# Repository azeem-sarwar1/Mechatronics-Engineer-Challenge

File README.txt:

KiCad PCB Design – Evaluation Task

This repository contains the PCB design created as part of the evaluation task using **KiCad**.

## 📌 Task Overview
1. **PCB Creation**
   - Added components:
     - Default KiCad LED symbol with footprint and 3D model is downloaded and modified.
     - Custom symbol + footprint for **TCAN4551-Q1** (VQFN-20 package) and 3D model is download.
     - Default KiCad symbol **MCIMX6D4AVT**.
     - Verified footprints with 3D viewer and picture attached.

2. **Custom Libraries**
   - Created a **custom symbol library** (`tcan4551-q1.kicad_sym`).
   - Created a **custom footprint library** (`TCAN4551_VQFN20.kicad_mod`).
   - Linked symbol and footprint.
   - 3D model is download.

3. **Design Rules**
   - Applied custom microvia design rules:
     - Minimum annular width: **2 mil**
     - Minimum via diameter: **8 mil**
     - Minimum via hole: **4 mil**

4. **Bonus**
   - Library for **TCAN4551-Q1** also stored in a separate repository, which can be mounted as a submodule.
    This project uses the TCAN4551 library. Download it separately from, https://github.com/azeem-sarwar1/TCAN4551-Q1_Library.git

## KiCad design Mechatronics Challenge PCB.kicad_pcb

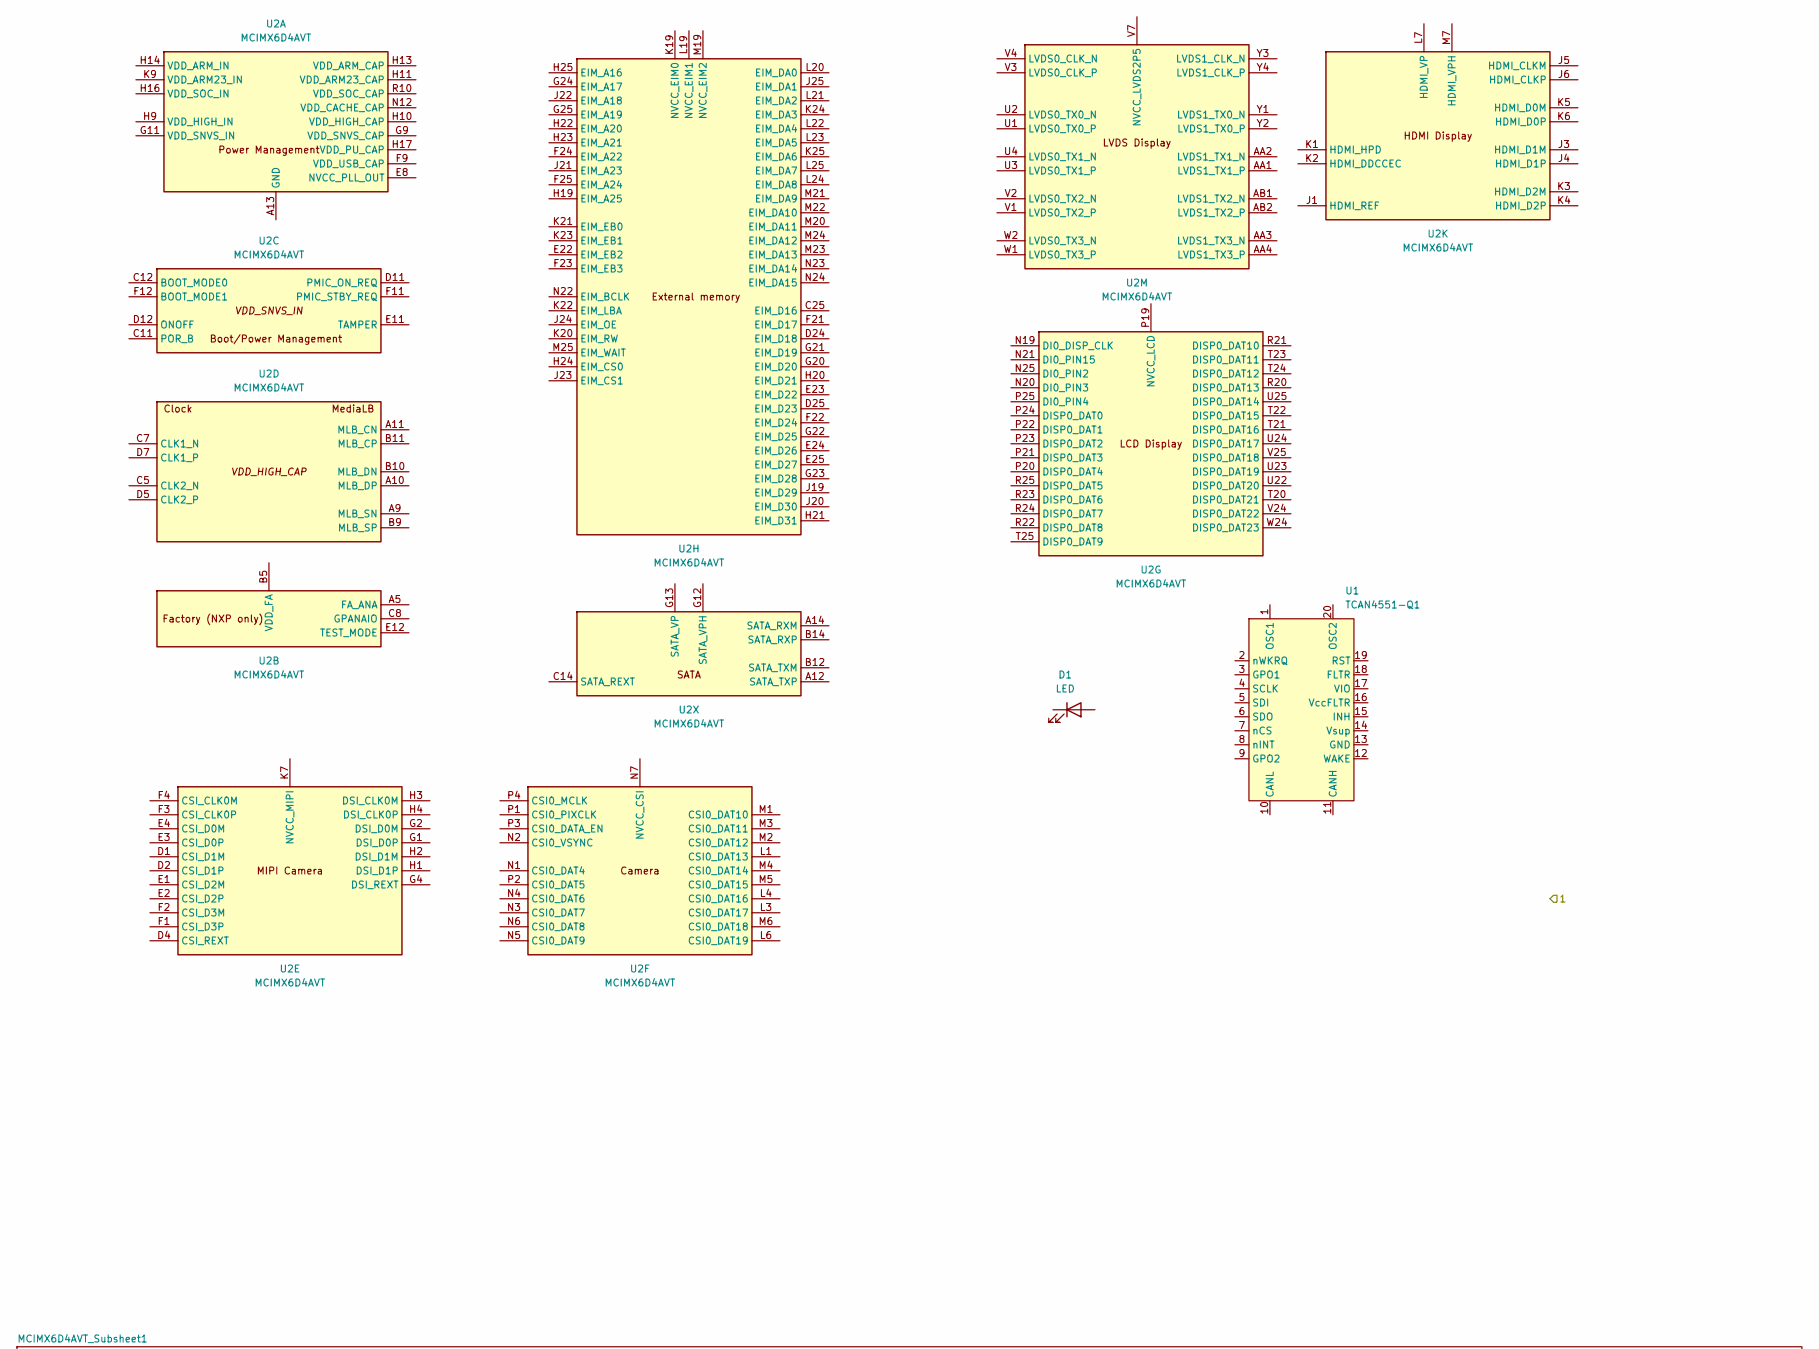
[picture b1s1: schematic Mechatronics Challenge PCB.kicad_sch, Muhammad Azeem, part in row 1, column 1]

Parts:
D1: LED; LED_miniPLCC_2315
U1: TCAN4551-Q1; TCAN4551_VQFN20
U2: MCIMX6D4AVT; BGA-624_21x21mm_Layout25x25_P0.8mm

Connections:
unnamed: U2.A4 (GND), U2.A8 (GND), U2.A13 (GND), U2.A25 (GND), U2.AA7 (GND), U2.AA10 (GND), U2.AA13 (GND), U2.AA16 (GND), U2.AA19 (GND), U2.AA22 (GND), U2.AB3 (GND), U2.AB24 (GND), U2.AD4 (GND), U2.AD7 (GND), U2.AD10 (GND), U2.AD13 (GND), U2.AD16 (GND), U2.AD19 (GND), U2.AD22 (GND), U2.AE1 (GND), U2.AE25 (GND), U2.B4 (GND), U2.C1 (GND), U2.C4 (GND), U2.C6 (GND), U2.C10 (GND), U2.D3 (GND), U2.D6 (GND), U2.D8 (GND), U2.E5 (GND), U2.E6 (GND), U2.E7 (GND), U2.F5 (GND), U2.F6 (GND), U2.F7 (GND), U2.F8 (GND), U2.G3 (GND), U2.G10 (GND), U2.G19 (GND), U2.H8 (GND), U2.H12 (GND), U2.H15 (GND), U2.H18 (GND), U2.J2 (GND), U2.J8 (GND), U2.J12 (GND), U2.J15 (GND), U2.J18 (GND), U2.K8 (GND), U2.K10 (GND), U2.K12 (GND), U2.K15 (GND), U2.K18 (GND), U2.L2 (GND), U2.L5 (GND), U2.L8 (GND), U2.L10 (GND), U2.L12 (GND), U2.L15 (GND), U2.L18 (GND), U2.M8 (GND), U2.M10 (GND), U2.M12 (GND), U2.M15 (GND), U2.M18 (GND), U2.N8 (GND), U2.N10 (GND), U2.N15 (GND), U2.N18 (GND), U2.P8 (GND), U2.P10 (GND), U2.P12 (GND), U2.P15 (GND), U2.P18 (GND), U2.R8 (GND), U2.R12 (GND), U2.R15 (GND), U2.R17 (GND), U2.T8 (GND), U2.T11 (GND), U2.T12 (GND), U2.T15 (GND), U2.T17 (GND), U2.T19 (GND), U2.U8 (GND), U2.U11 (GND), U2.U12 (GND), U2.U15 (GND), U2.U17 (GND), U2.U19 (GND), U2.V8 (GND), U2.V19 (GND), U2.W3 (GND), U2.W7 (GND), U2.W8 (GND), U2.W9 (GND), U2.W10 (GND), U2.W11 (GND), U2.W12 (GND), U2.W13 (GND), U2.W15 (GND), U2.W16 (GND), U2.W17 (GND), U2.W18 (GND), U2.W19 (GND), U2.Y5 (GND), U2.Y24 (GND)
unnamed: U2.H11 (VDD_ARM23_CAP), U2.J11 (VDD_ARM23_CAP), U2.K11 (VDD_ARM23_CAP), U2.L11 (VDD_ARM23_CAP), U2.M11 (VDD_ARM23_CAP), U2.N11 (VDD_ARM23_CAP), U2.P11 (VDD_ARM23_CAP), U2.R11 (VDD_ARM23_CAP)
unnamed: U2.K9 (VDD_ARM23_IN), U2.L9 (VDD_ARM23_IN), U2.M9 (VDD_ARM23_IN), U2.N9 (VDD_ARM23_IN), U2.P9 (VDD_ARM23_IN), U2.R9 (VDD_ARM23_IN), U2.T9 (VDD_ARM23_IN), U2.U9 (VDD_ARM23_IN)
unnamed: U2.H13 (VDD_ARM_CAP), U2.J13 (VDD_ARM_CAP), U2.K13 (VDD_ARM_CAP), U2.L13 (VDD_ARM_CAP), U2.M13 (VDD_ARM_CAP), U2.N13 (VDD_ARM_CAP), U2.P13 (VDD_ARM_CAP), U2.R13 (VDD_ARM_CAP)
unnamed: U2.H14 (VDD_ARM_IN), U2.J14 (VDD_ARM_IN), U2.K14 (VDD_ARM_IN), U2.L14 (VDD_ARM_IN), U2.M14 (VDD_ARM_IN), U2.N14 (VDD_ARM_IN), U2.P14 (VDD_ARM_IN), U2.R14 (VDD_ARM_IN)
unnamed: U2.H10 (VDD_HIGH_CAP), U2.J10 (VDD_HIGH_CAP)
unnamed: U2.H9 (VDD_HIGH_IN), U2.J9 (VDD_HIGH_IN)
unnamed: U2.H17 (VDD_PU_CAP), U2.J17 (VDD_PU_CAP), U2.K17 (VDD_PU_CAP), U2.L17 (VDD_PU_CAP), U2.M17 (VDD_PU_CAP), U2.N17 (VDD_PU_CAP), U2.P17 (VDD_PU_CAP)
unnamed: U2.R10 (VDD_SOC_CAP), U2.T10 (VDD_SOC_CAP), U2.T13 (VDD_SOC_CAP), U2.T14 (VDD_SOC_CAP), U2.U10 (VDD_SOC_CAP), U2.U13 (VDD_SOC_CAP), U2.U14 (VDD_SOC_CAP)
unnamed: U2.H16 (VDD_SOC_IN), U2.J16 (VDD_SOC_IN), U2.K16 (VDD_SOC_IN), U2.L16 (VDD_SOC_IN), U2.M16 (VDD_SOC_IN), U2.N16 (VDD_SOC_IN), U2.P16 (VDD_SOC_IN), U2.R16 (VDD_SOC_IN), U2.T16 (VDD_SOC_IN), U2.U16 (VDD_SOC_IN)

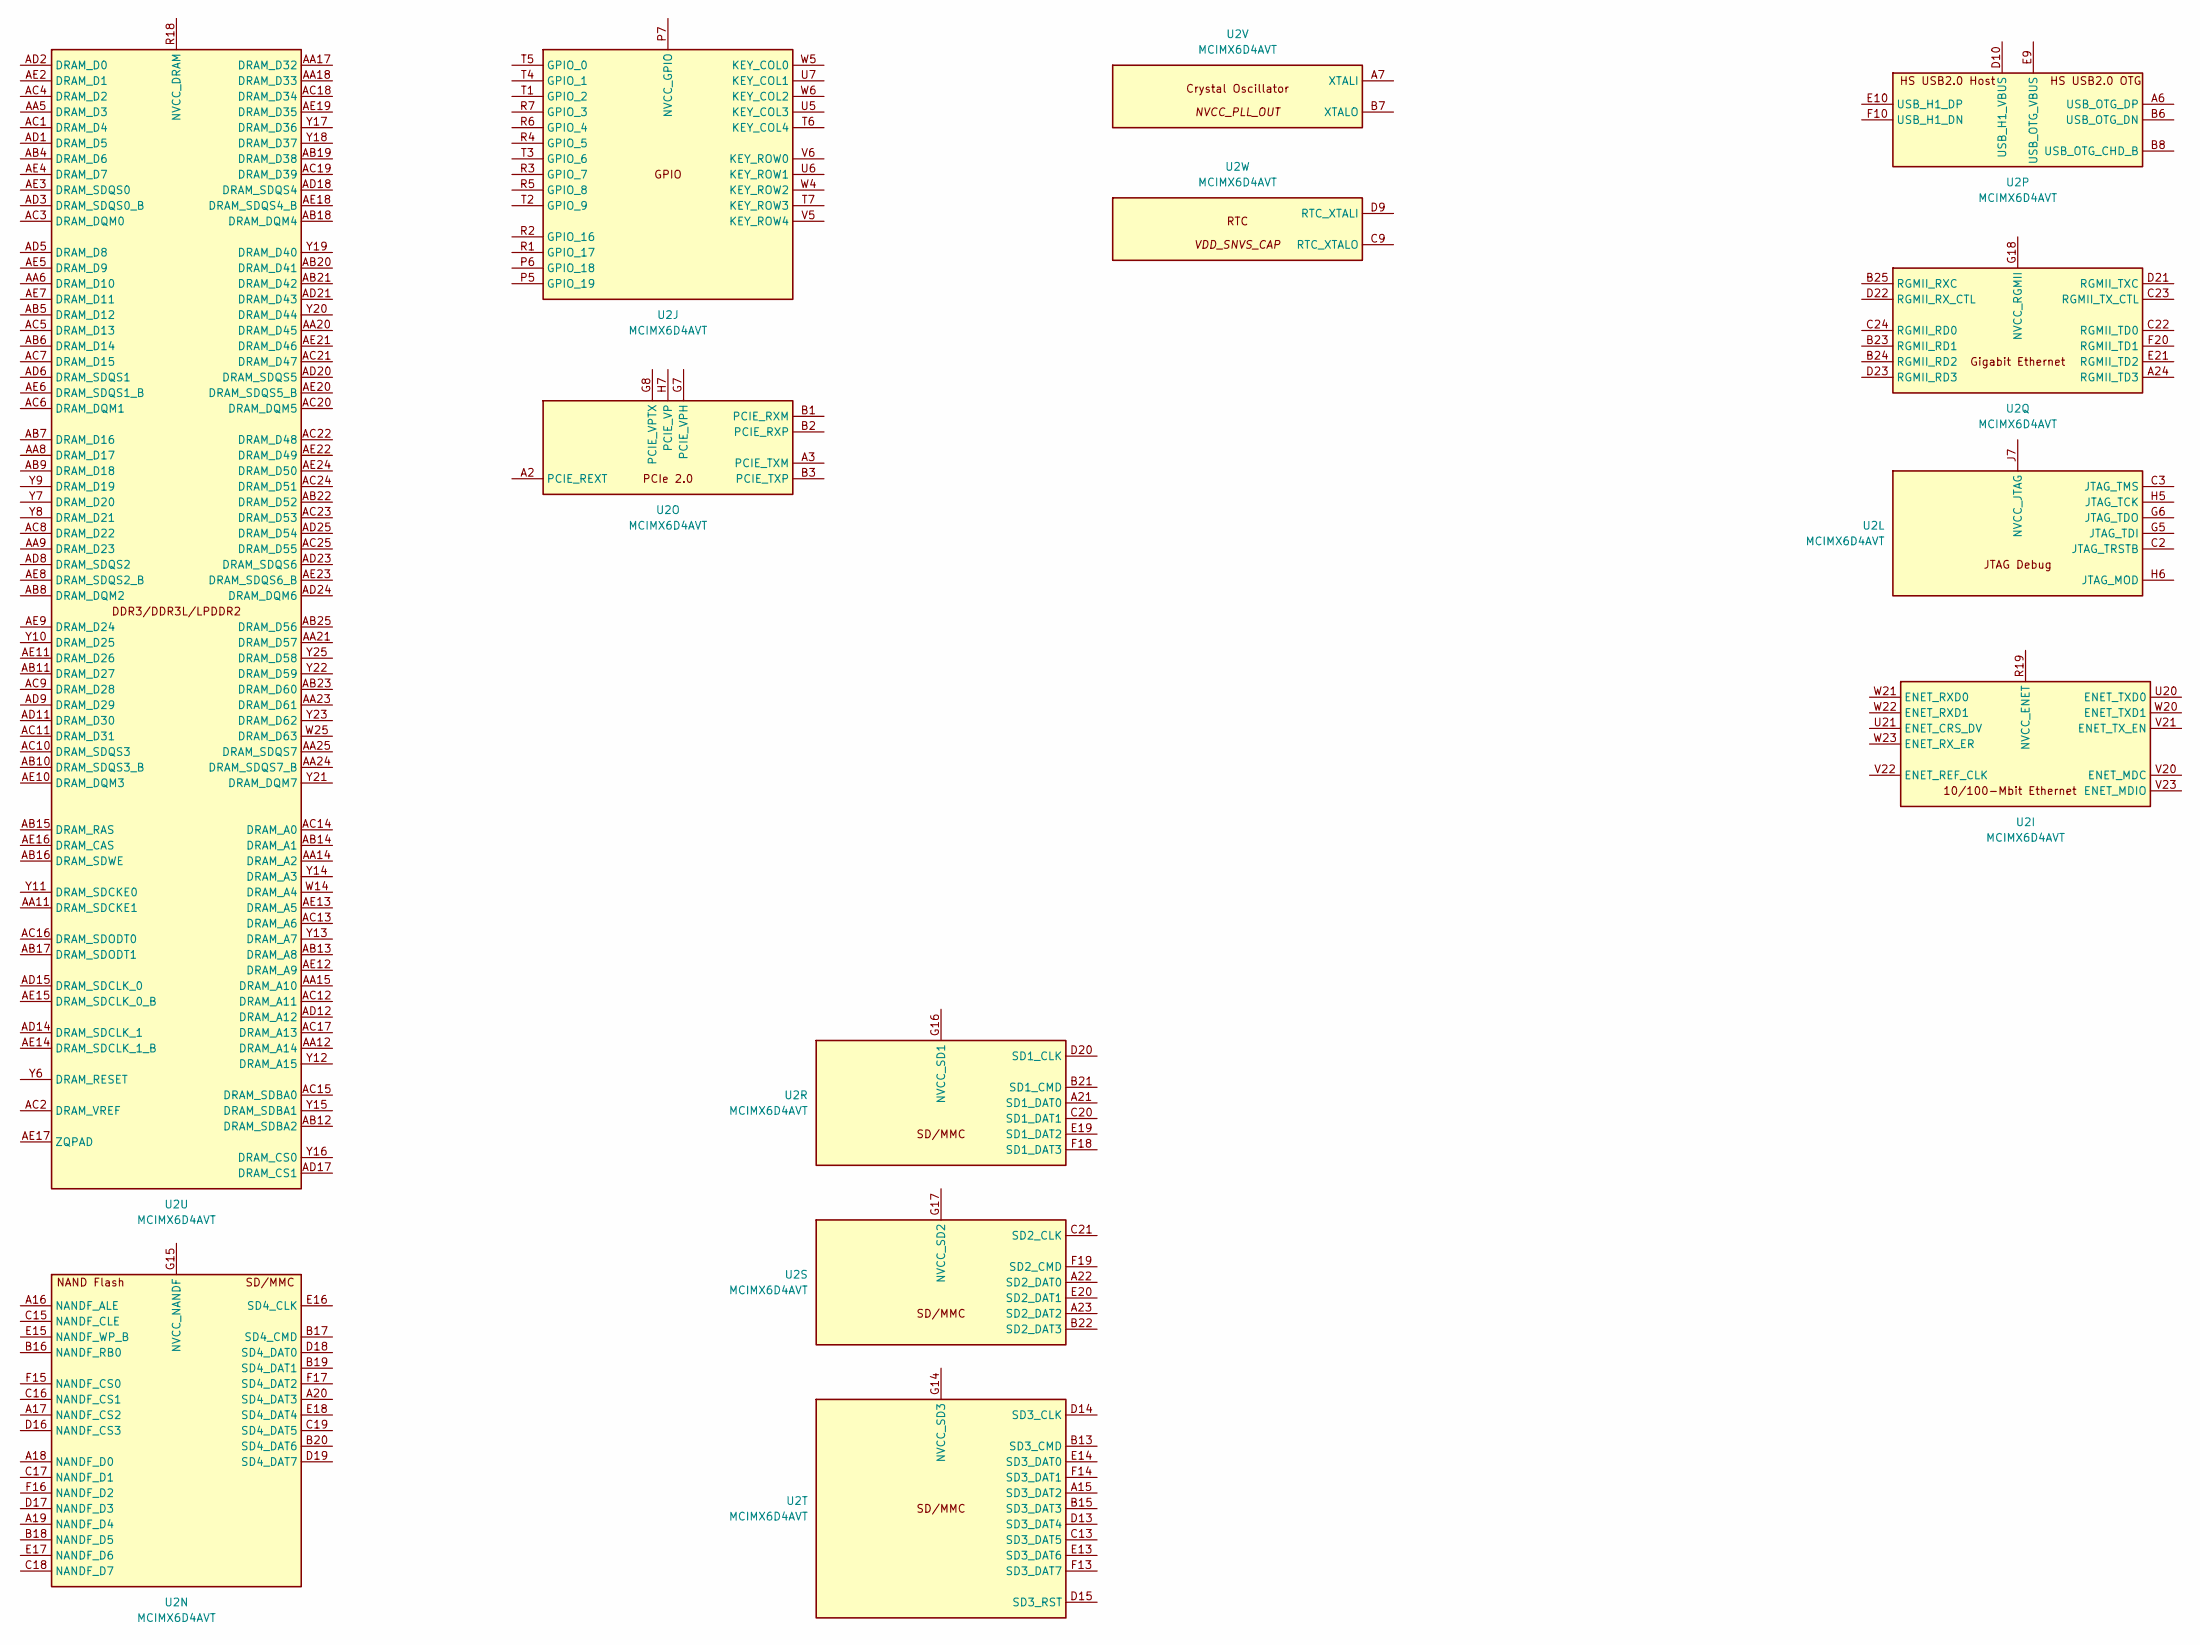
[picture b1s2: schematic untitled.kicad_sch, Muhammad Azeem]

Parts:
U2: MCIMX6D4AVT; BGA-624_21x21mm_Layout25x25_P0.8mm

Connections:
unnamed: U2.R18 (NVCC_DRAM), U2.T18 (NVCC_DRAM), U2.U18 (NVCC_DRAM), U2.V9 (NVCC_DRAM), U2.V10 (NVCC_DRAM), U2.V11 (NVCC_DRAM), U2.V12 (NVCC_DRAM), U2.V13 (NVCC_DRAM), U2.V14 (NVCC_DRAM), U2.V15 (NVCC_DRAM), U2.V16 (NVCC_DRAM), U2.V17 (NVCC_DRAM), U2.V18 (NVCC_DRAM)

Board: 2 copper layers, 3 parts (0 on the bottom side), 11 nets, no tracks yet.

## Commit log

2025-09-28 Create .gitmodules
    TCAN4551-Q1_Library
